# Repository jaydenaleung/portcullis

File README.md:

# Portcullis - the boltlock unlocker

A portcullis originally guarded a castle's entrance, known for its waffle-like iron gates coming down to cover the entrance of the castle's archway following the moat bridge.
-

Portcullis is an automated system that mechanically unlocks home security door reinforcement locks (HSDRLs), with access protected by a passcode using a keypad. HSDRLs act as boltlocks when mounted onto the doorframe next to the door being locked. See below for more information.

VIDEO DEMO: [https://youtu.be/WndzgAl9owI](url)

*The large block in the picture represents the wall that HSDRLs are mounted onto.*

*A medival portcullis. Credit: [https://www.dreamstime.com/stock-images-castle-portcullis-image7831724](url).*

# Figures

**Total Minimum Cost:** $43 USD

**Total Hours Spent:** 92 hrs

**Total Days Spent:** 16 days

*See JOURNAL.md and the BOM below for an in-depth explanation of these numbers.*

# How It Works

How do HSDRLs work?
-

HSDRLs lock a door by acting as a fixed stopper. In combination with this, their tough metal material allows it to be one of the strongest, safest, and most secure locks on the market. After turning them to their locked position, they will 'click' into place, effectively fixing itself against the door. Mechanically, this means that when the door pushes against it, its rigid position will hold the door back. See the picture below for how unlocking and locking an HSDRL works.

Portcullis
-

This specific mechanism works to solve this issue in three steps: one, using a linear actuator to push the HSDRL forward enough that it can be rotated. Two, rotate it to unlock or lock the door. Three, retract the linear actuator to lock the HSDRL in place. This is all controlled by an Arduino Uno R3 microcontroller, which connects to a continuous servo powering the linear actuator and a positional servo rotating the mechanism. Additionally, the locking/unlocking process is initiated by either entering the correct passcode on a keypad on the side of the door opposite the lock or by pressing a button (passcode not required) on the same side of the door as the lock.

Additional Features
-

- 16x2 LCD interface to display entered PIN from the keypad
- Privacy covers when entering PIN - numbers show up as '*' instead of the entered number
- Three different possible screens for the LCD display
- Aesthetic microcontroller housing with LED lights on button
- Linear guide rails and tension springs for the linear actuator

Wiring Diagram
-

This project does not utilize a PCB because of the sparse placement of the connected parts. See this wiring diagram instead:

And this schematic:

# The 'Why' Behind the Project

This project actually started a while ago when I wanted to ensure that no one would could come into my room without my permission, as I felt back then that it had become an issue. Using my engineering skills to solve real-world issues, I initially worked on developing my own boltlock before realizing that it would be much more efficient to just purchase a boltlock. Unfortunately, I would occasionally get locked out of my room, which was a significant issue. I again began to solve this issue by taking an engineering approach to it and working a system that could lock and unlock the boltlock for me when I was outside of my room. In addition to having a keypad, I envision pairing this mechanism with my phone so that it will be more easily accessible, especially if something happens to break or the wires to the keypad snap.

# Why This Is Worth Six Points

With the three-part unlocking/locking system mentioned earlier, this is a mechanically complex project that requires precise control of the motors in order to ensure reliability and stability. I spent many hours designing a system for this (over half of my hours spent were in CAD and research), learning a lot about linear guide rails, springs, and their standardizations, and how to effectively approach a real-life issue using engineering. Additionally, I spent a significant amount of time and effort designing logic for the keypad, LCD screens, and LED button as well as making them all work smoothly in tandem. My effort spent doing this project, seen in the thirty hours of work done in addition to prior work and excluding the process of physically building the device, qualifies this project for six points.

# Bill of Materials (BOM):

*Note: I am using Aliexpress for some and Amazon for others. Prices listed below are in USD and per part. e.g. 2x Nema 17 ($14) = $28 total. Also see the .csv file for the official BOM.*

| Quantity | Name | Price Per Part | Link | Notes |
|---|---|---|---|---|
| 2 | MGN7C linear guide rail + carriage | $12.78 | https://www.aliexpress.us/item/3256804722090559.html | 150mm length |
| 4 | M2 50pcs bolt | $1.27 | https://www.aliexpress.us/item/2255799955713291.html | 4mm, 6mm, 8mm, 10mm lengths |
| 1 | M2 50pcs nut | $1.52 | https://www.aliexpress.us/item/3256807407546447.html |  |
| 1 | M3 30pcs bolt | $1.43 | https://www.aliexpress.us/item/2255799955713291.html | 6mm length |
| 1 | M3 50pcs nut | $1.68 | https://www.aliexpress.us/item/3256807407546447.html |  |
| 1 | 10 pcs Tension spring w/ hook | $4.09 | http://www.aliexpress.us/item/3256805190632211.html | 50mm length, 0.3mm wire diameter, 5mm outer diameter |
| 2 | Pushbutton | $3.06 | https://www.aliexpress.us/item/3256807837994773.html | Red color (NOT with the power symbol), 3-6V, 19mm size, momentary type |
| 1 | 3m length wire cover | $5.39 | https://www.aliexpress.us/item/3256808858896776.html | A-White (A-type, white and red color) |
| 1 | Heat gun + Heat shrink tubes | $9.99 | https://www.aliexpress.us/item/3256807579039319.html | 1060 pcs, 110V US plug |
| 1 | Keypad | N/A | https://a.co/d/2Og2Gza | Already have this (no price). |
| 1 | LCD | $2.39 | https://www.aliexpress.us/item/3256806852105736.html | I2C LCD Green |
| 1 | Power bank + USB-B cable | N/A | Any works | Already have this (no price). |
| 1 | Positional SG90 Servo | N/A | https://a.co/d/dwwxeeT | Already have this (no price). |
| 1 | Continuous FS90R Servo | N/A | https://a.co/d/2raoKgm | Already have this (no price). |
| 1 | Jumper wires | N/A | https://a.co/d/hYEySLh | Already have this (no price). |
| 1 | 1kg spool of filament | N/A | Any works | Any color, any type. Already have this (no price). |
| 1 | Home security door reinforcement lock | N/A | https://a.co/d/iCTK5DP | Already have this (no price). |
| 1 | 330Ω resistor | N/A | N/A | Already have this (no price). |

| **Total minimum cost** | $43.41 |
| --------------------------------------------------- | ---- |
| **Total including shipping; sales tax (assumed ~6%); import and customs fees; etc.** | ~$75 |

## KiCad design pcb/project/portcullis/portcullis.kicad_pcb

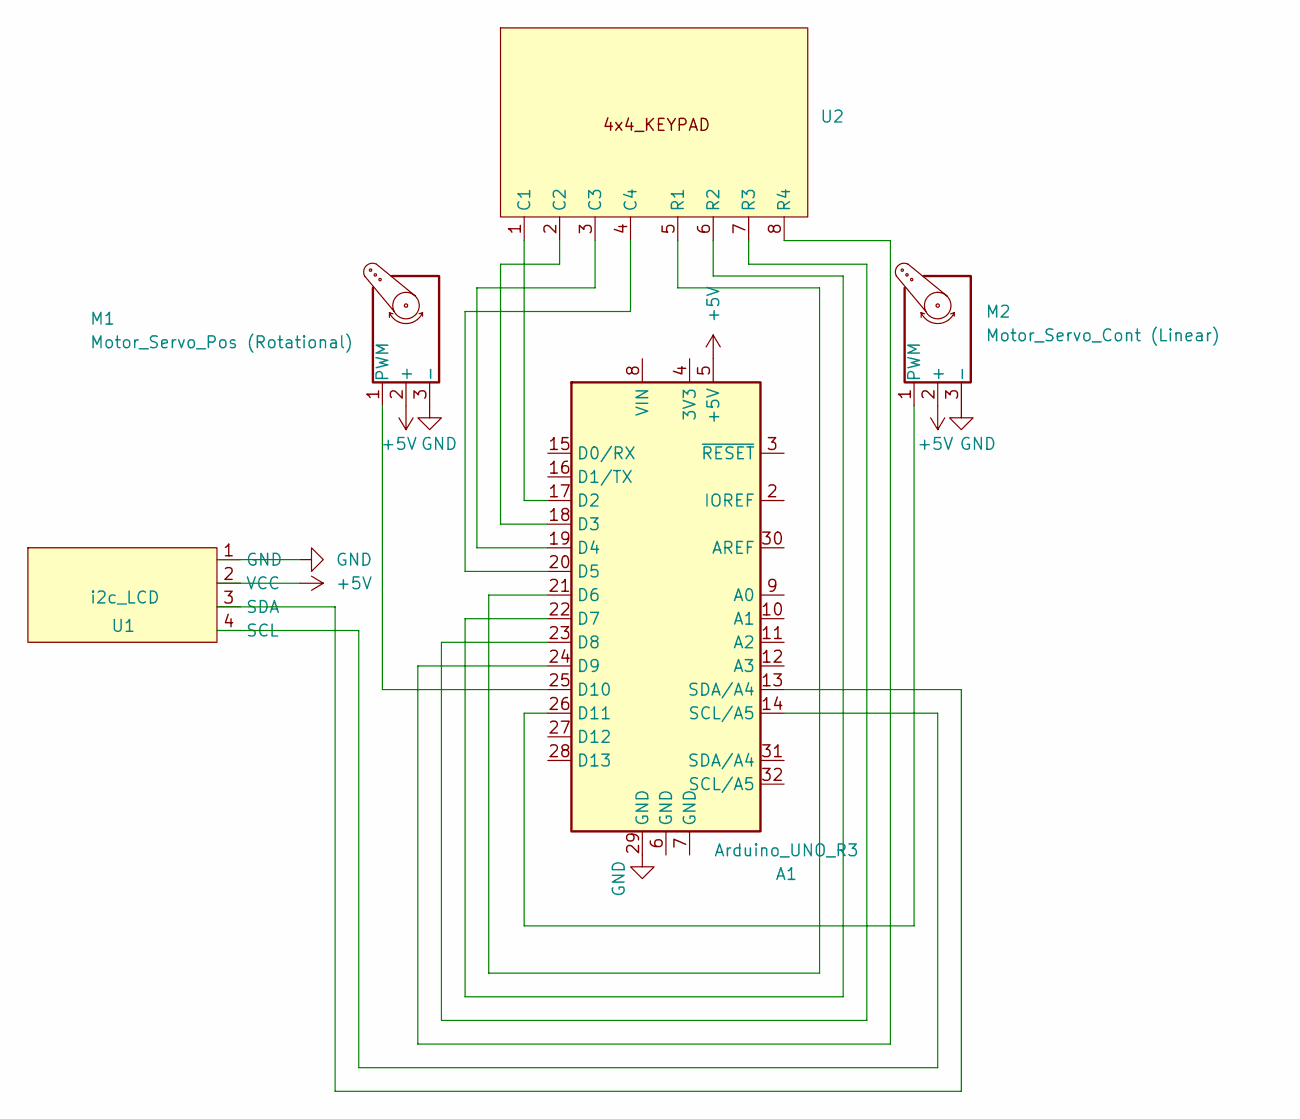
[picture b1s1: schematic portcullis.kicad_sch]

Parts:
A1: Arduino_UNO_R3; ARDUINO_ARDUINO_UNO_REV3
M1: Motor_Servo_Pos (Rotational); 3-Pin Servo
M2: Motor_Servo_Cont (Linear); 3-Pin Servo
U1: i2c_LCD
U2: 4x4 16 Button Keypad

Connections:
+5V: A1.5 (+5V), M1.2 (+), M2.2 (+), U1.2 (VCC)
GND: A1.29 (GND), M1.3 (-), M2.3 (-), U1.1 (GND)
unnamed: A1.17 (D2), U2.1 (C1)
unnamed: A1.18 (D3), U2.2 (C2)
unnamed: A1.19 (D4), U2.3 (C3)
unnamed: A1.20 (D5), U2.4 (C4)
unnamed: A1.21 (D6), U2.5 (R1)
unnamed: A1.22 (D7), U2.6 (R2)
unnamed: A1.23 (D8), U2.7 (R3)
unnamed: A1.24 (D9), U2.8 (R4)
unnamed: A1.25 (D10), M1.1 (PWM)
unnamed: A1.26 (D11), M2.1 (PWM)
unnamed: A1.14 (SCL/A5), U1.4 (SCL)
unnamed: A1.13 (SDA/A4), U1.3 (SDA)

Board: 2 copper layers, 5 parts (1 on the bottom side), 14 nets, no tracks yet.

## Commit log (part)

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2025-07-06 work
2025-07-07 setup journal
2025-07-07 Update JOURNAL
2025-07-07 kicad
2025-07-08 pcb finish pt 1
2025-07-08 change to markdown
2025-07-09 pushbutton
2025-07-09 firmware
2025-07-10 final
2025-07-11 cad and readme
2025-07-16 added gcodes
2025-08-08 Update cad files and assembly for jounal
2025-08-18 Update hours (forgot to before)
